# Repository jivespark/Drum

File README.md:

# Drum
This is going to be my project for week 3 of Hack Club half life. I built this project, because the task was to make an instrument, and I thought it would be cool to build a custom drum pad with a speaker to play the sounds.

## Design process:  
My first idea was that I just want to make a bunch of buttons for the drums, and a speaker to play all the sounds. The finished design was something pretty close to that, the only main difference from the original design, was that instead of regular buttons, I made custom footprints for capacitive touch buttons, directly in the PCB, so that I could have them in any shape/ layout that I wanted. I originally wanted to make a wider layout, with bigger buttons, but to fit within the JLCPC 100x100mm deal, I had to make it smaller, otherwise it would have been too expensive. After that the rest was pretty easy, I used an amplifier and a 40 mm speaker for the sound, and for the microcontroller I went with an ESP32 for it's capacitive touch inputs, and enough power to handle the audio files.

## Assembly+firmware:  
To assemble you just need to solder everything into the PCB, since all components are through hole, it shouldn't be too hard. You just need to screw the case on using M3 screws, and pop the speaker into the hole designed for it(note that the speaker hole might not be accurate, since I don't have the exact speaker yet, and they had no technical drawing available) The firmware is running on circuitpython, and can be downloaded [here](https://circuitpython.org/board/seeed_xiao_esp32s3/), after flashing that, you just need to upload everything in the firmware folder(code.py and the sounds folder) to the board, and you should be done.(note that the capacitive touch sensing may  need to be calibrated, but since I haven't built the project yet, I can't test exact calibration settings. This will be updated when I build the project).

## Images:  
Cad render:  

Schematic:  

PCB:  

##BOM
| Item                     | Qty | Supplier   | Cost/item | Total Cost | link                                                  |
|--------------------------|-----|------------|-----------|------------|-------------------------------------------------------|
| XIAO ESP32-S3            | 1   | Aliexpress | $10.57    | $10.57     | https://www.aliexpress.com/item/1005007870593864.html |
| MAX98357 audio amplifier | 1   | Aliexpress | $1.62     | $1.62      | https://www.aliexpress.com/item/1005009356741606.html |
| 40mm speaker             | 1   | Aliexpress | $2.86     | $2.86      | https://www.aliexpress.com/item/1005006335969407.html |
| PCB                      | 1   | JLCPCB     | $4.00     | $4.00      | https://jlcpcb.com/quote                              |
| Screws                   | 1   | Aliexpress | $2.08     | $2.08      | https://www.aliexpress.com/item/4000117933430.html    |
| Estimated total shipping | 1   |            |           | $9.00      |                                                       |

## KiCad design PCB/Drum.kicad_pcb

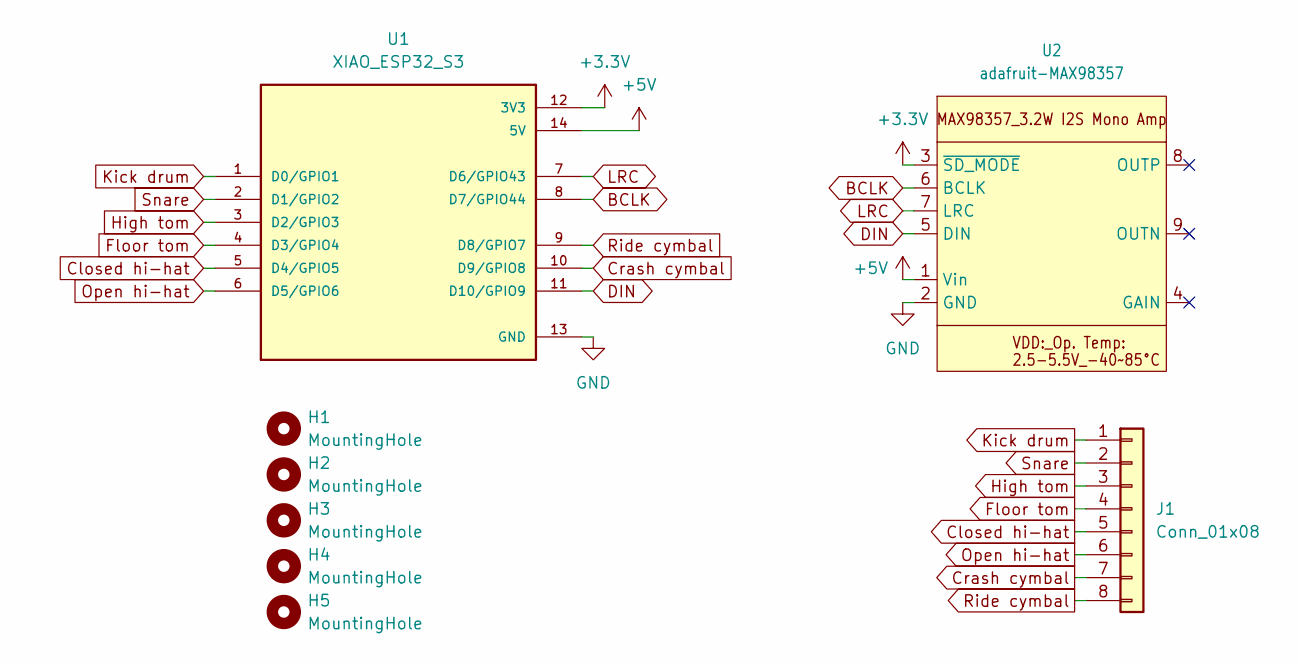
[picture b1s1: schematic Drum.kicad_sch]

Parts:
H1, H2, H3, H4, H5: MountingHole; MountingHole_3.2mm_M3
J1: Conn_01x08; Drum buttons
U1: XIAO_ESP32_S3; MODULE_XIAO_ESP32_S3; PARTREV April 22nd, 2026
U2: adafruit-MAX98357

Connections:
+3.3V: U1.12 (3V3), U2.3 (~SD_MODE)
+5V: U1.14 (5V), U2.1 (Vin)
BCLK: U1.8 (D7/GPIO44), U2.6 (BCLK)
Closed hi-hat: J1.5, U1.5 (D4/GPIO5)
Crash cymbal: J1.7, U1.10 (D9/GPIO8)
DIN: U1.11 (D10/GPIO9), U2.5 (DIN)
Floor tom: J1.4, U1.4 (D3/GPIO4)
GND: U1.13 (GND), U2.2 (GND)
High tom: J1.3, U1.3 (D2/GPIO3)
Kick drum: J1.1, U1.1 (D0/GPIO1)
LRC: U1.7 (D6/GPIO43), U2.7 (LRC)
Open hi-hat: J1.6, U1.6 (D5/GPIO6)
Ride cymbal: J1.8, U1.9 (D8/GPIO7)
Snare: J1.2, U1.2 (D1/GPIO2)

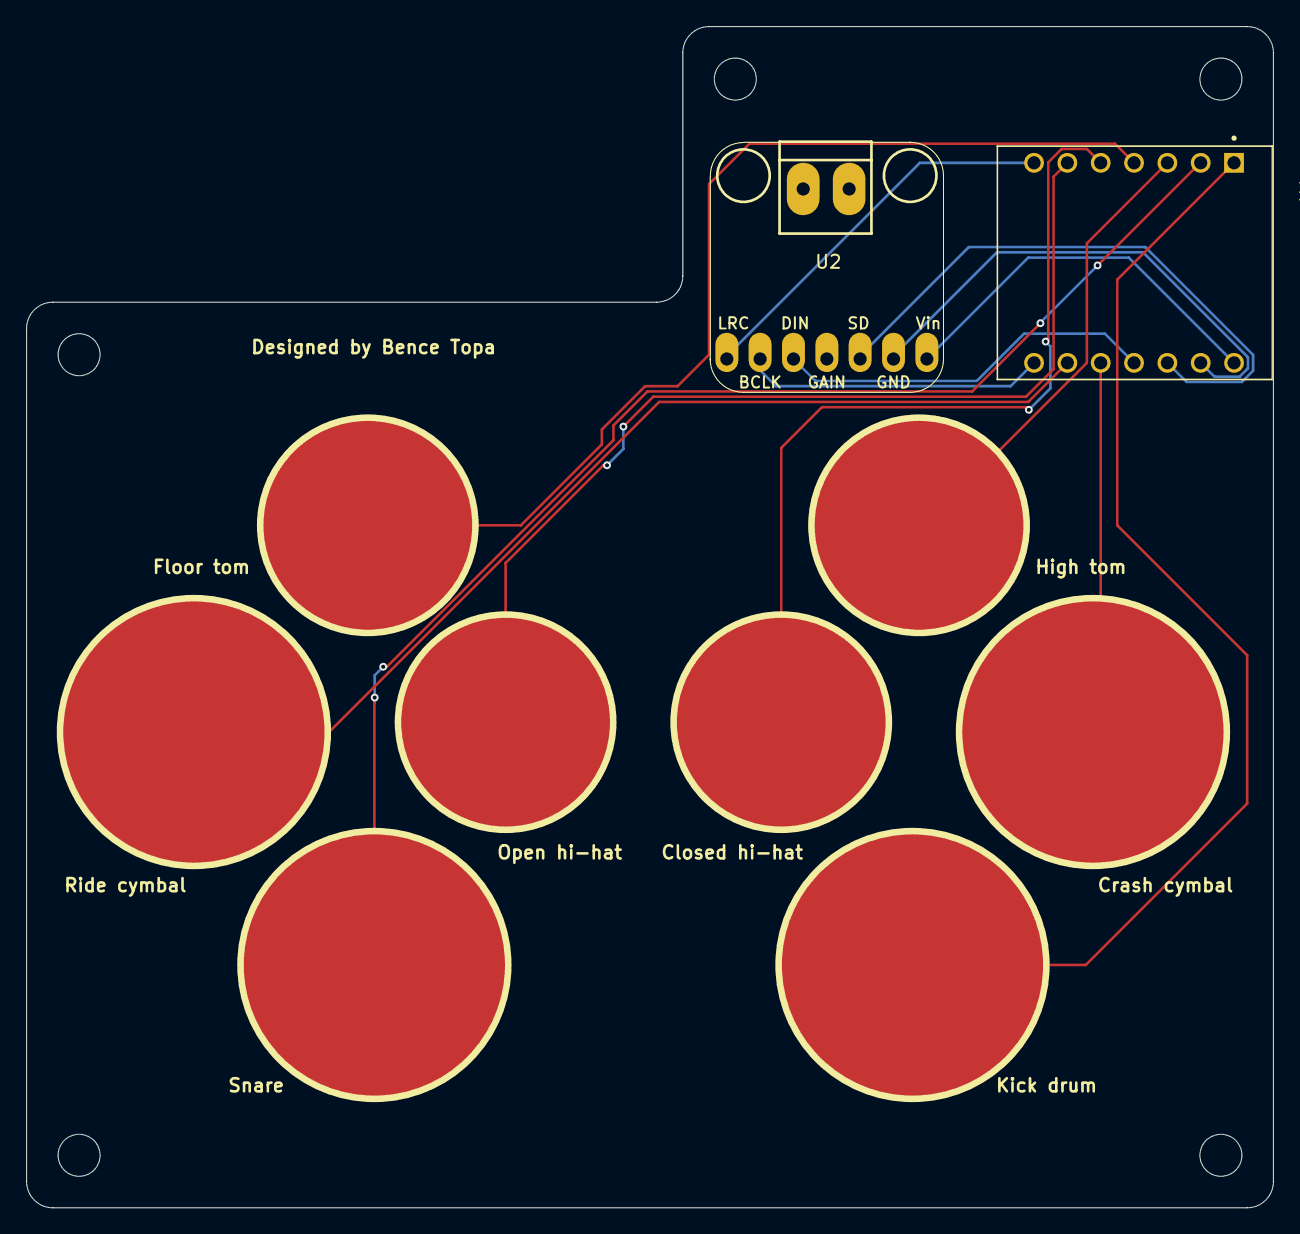
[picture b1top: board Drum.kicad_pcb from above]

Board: 2 copper layers, 95.0 x 90.0 mm, 8 parts (0 on the bottom side), 14 nets.
